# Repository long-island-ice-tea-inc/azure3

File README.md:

azure3
======

Engineering an 8x8x8 LED Cube

Directory Structure:
```
  azure3
     |
     +-----> pcb
     +-----> cam
     +-----> rpi
     |        |
     |        +----> lib
     |        |       |
     |        |       +----> bcm2835
     |        +----> src
     +-----> de1
```

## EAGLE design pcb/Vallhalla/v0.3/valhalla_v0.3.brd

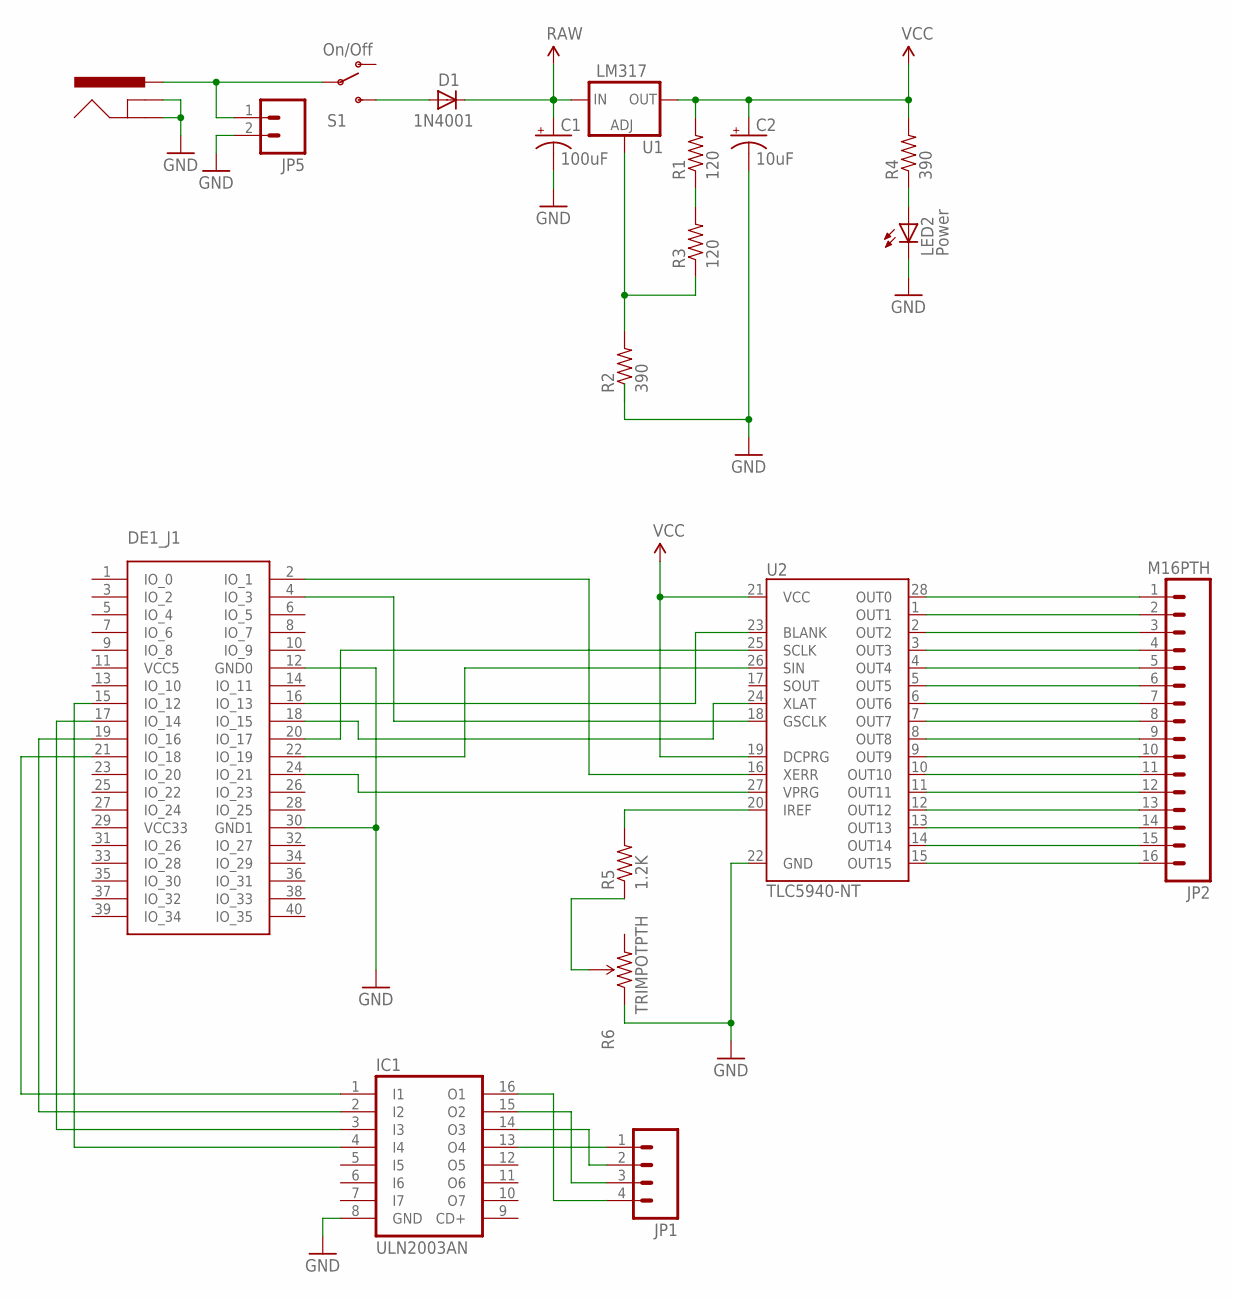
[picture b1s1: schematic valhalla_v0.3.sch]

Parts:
C1: 100uF; CPOL-RADIAL-100UF-25V
C2: 10uF; CPOL-RADIAL-10UF-25V
D1: 1N4001; DIODE-0.4
DE1_J1: DE1_GPIO_CON40"; 2X20
IC1: ULN2003AN; DIL16
J1: POWER_JACKPTH; POWER_JACK_PTH
JP1: M04PTH; 1X04
JP2: M16PTH; 1X16
JP5: M02PTH; 1X02
LED2: Power; LED5MM
R1, R3: 120; AXIAL-0.3
R2, R4: 390; AXIAL-0.3
R5: 1.2K; AXIAL-0.5
R6: TRIMPOTPTH; TRIM_POT_PTH
S1: On/Off; SWITCH-SPST
U1: LM317; TO220-ADJ
U2: TLC5940-NT; DIL28-3

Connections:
BLANK: DE1_J1.16 (IO_13), U2.23 (BLANK)
GND: C1.2 (-), C2.2 (-), DE1_J1.12 (GND0), DE1_J1.30 (GND1), IC1.8 (GND), J1.GND, J1.GNDBREAK, JP5.2, LED2.K (C), R2.P$1 (1), R6.1 (CCW), U2.22 (GND)
GSCLK: DE1_J1.4 (IO_3), U2.18 (GSCLK)
IREF: R5.P$2 (2), U2.20 (IREF)
unnamed: JP2.16, U2.15 (OUT15)
unnamed: D1.A, S1.3 (S)
unnamed: J1.PWR, JP5.1, S1.2
unnamed: JP2.15, U2.14 (OUT14)
unnamed: R5.P$1 (1), R6.2 (WIPER)
unnamed: JP2.14, U2.13 (OUT13)
unnamed: JP2.13, U2.12 (OUT12)
unnamed: LED2.A, R4.P$1 (1)
unnamed: JP2.12, U2.11 (OUT11)
unnamed: JP2.11, U2.10 (OUT10)
unnamed: JP2.10, U2.9 (OUT9)
unnamed: JP2.9, U2.8 (OUT8)
unnamed: JP2.8, U2.7 (OUT7)
unnamed: JP2.7, U2.6 (OUT6)
unnamed: JP2.6, U2.5 (OUT5)
unnamed: JP2.5, U2.4 (OUT4)
unnamed: JP2.4, U2.3 (OUT3)
unnamed: JP2.3, U2.2 (OUT2)
unnamed: JP2.2, U2.1 (OUT1)
unnamed: JP2.1, U2.28 (OUT0)
unnamed: DE1_J1.15 (IO_12), IC1.4 (I4)
unnamed: R1.P$1 (1), R3.P$2 (2)
unnamed: DE1_J1.17 (IO_14), IC1.3 (I3)
unnamed: R2.P$2 (2), R3.P$1 (1), U1.ADJ
unnamed: DE1_J1.19 (IO_16), IC1.2 (I2)
unnamed: DE1_J1.21 (IO_18), IC1.1 (I1)
unnamed: IC1.13 (O4), JP1.1
unnamed: IC1.14 (O3), JP1.2
unnamed: IC1.15 (O2), JP1.3
unnamed: IC1.16 (O1), JP1.4
RAW: C1.1 (+), D1.C, U1.IN
SCLK: DE1_J1.20 (IO_17), U2.25 (SCLK)
SIN: DE1_J1.22 (IO_19), U2.26 (SIN)
VCC: C2.1 (+), R1.P$2 (2), R4.P$2 (2), U1.OUT, U2.19 (DCPRG), U2.21 (VCC)
VCC5: DE1_J1.11 (VCC5)
VCC33: DE1_J1.29 (VCC33)
VPRG: DE1_J1.24 (IO_21), U2.27 (VPRG)
XERR: DE1_J1.2 (IO_1), U2.16 (XERR)
XLAT: DE1_J1.18 (IO_15), U2.24 (XLAT)

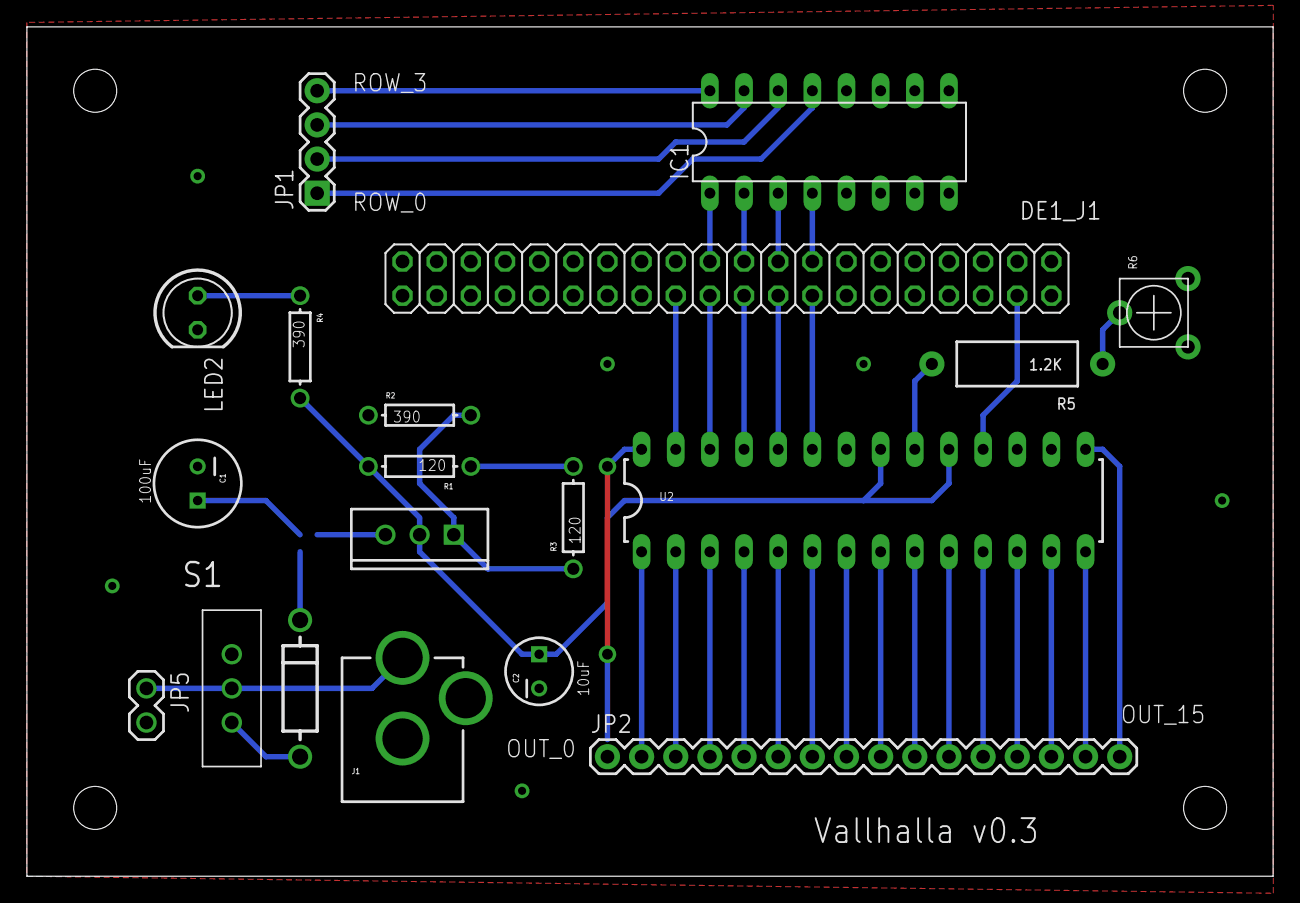
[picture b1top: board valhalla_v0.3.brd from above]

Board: 2 copper layers, 92.7 x 63.2 mm, 19 parts (0 on the bottom side), 41 nets.

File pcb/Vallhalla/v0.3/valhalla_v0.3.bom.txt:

Partlist exported from E:/WorK/github/azure3/pcb/Vallhalla/v0.3/valhalla_v0.3.sch at 3/5/2016 3:25 AM

Part   Value         Device           Package               Description                                                         
C1     100uF         CAP_POLPTH1      CPOL-RADIAL-100UF-25V Capacitor Polarized                                                 
C2     10uF          CAP_POLPTH2      CPOL-RADIAL-10UF-25V  Capacitor Polarized                                                 
D1     1N4001        DIODEPTH         DIODE-0.4             Diode                                                               
DE1_J1               DE1_GPIO_CON40"  2X20                  DE1 GPIO Connector                                                  
IC1    ULN2003AN     ULN2003AN        DIL16                 DRIVER ARRAY                                                        
J1     POWER_JACKPTH POWER_JACKPTH    POWER_JACK_PTH        Power Jack                                                          
JP1                  M04PTH           1X04                  Header 4                                                            
JP2    M16PTH        M16PTH           1X16                  1x16 .1" header                                                     
JP5                  M02PTH           1X02                  Header 2                                                            
LED2   Power         LED5MM           LED5MM                                                                                    
R1     120           RESISTORPTH1     AXIAL-0.3             Resistor                                                            
R2     390           RESISTORPTH1     AXIAL-0.3             Resistor                                                            
R3     120           RESISTORPTH1     AXIAL-0.3             Resistor                                                            
R4     390           RESISTORPTH1     AXIAL-0.3             Resistor                                                            
R5     1.2K          RESISTORPTH-1/2W AXIAL-0.5             Resistor                                                            
R6     TRIMPOTPTH    TRIMPOTPTH       TRIM_POT_PTH          Various small potentiometers for "set-and-forget" applications      
S1     On/Off        SWITCH-SPSTPTH   SWITCH-SPST           SPST Switch                                                         
U1     LM317         V_REG_317SINK    TO220-ADJ             Voltage Regulator                                                   
U2     TLC5940-NT    TLC5940-NT       DIL28-3               16-channel LED Driver with Dot Correction and Grayscale PWM Control

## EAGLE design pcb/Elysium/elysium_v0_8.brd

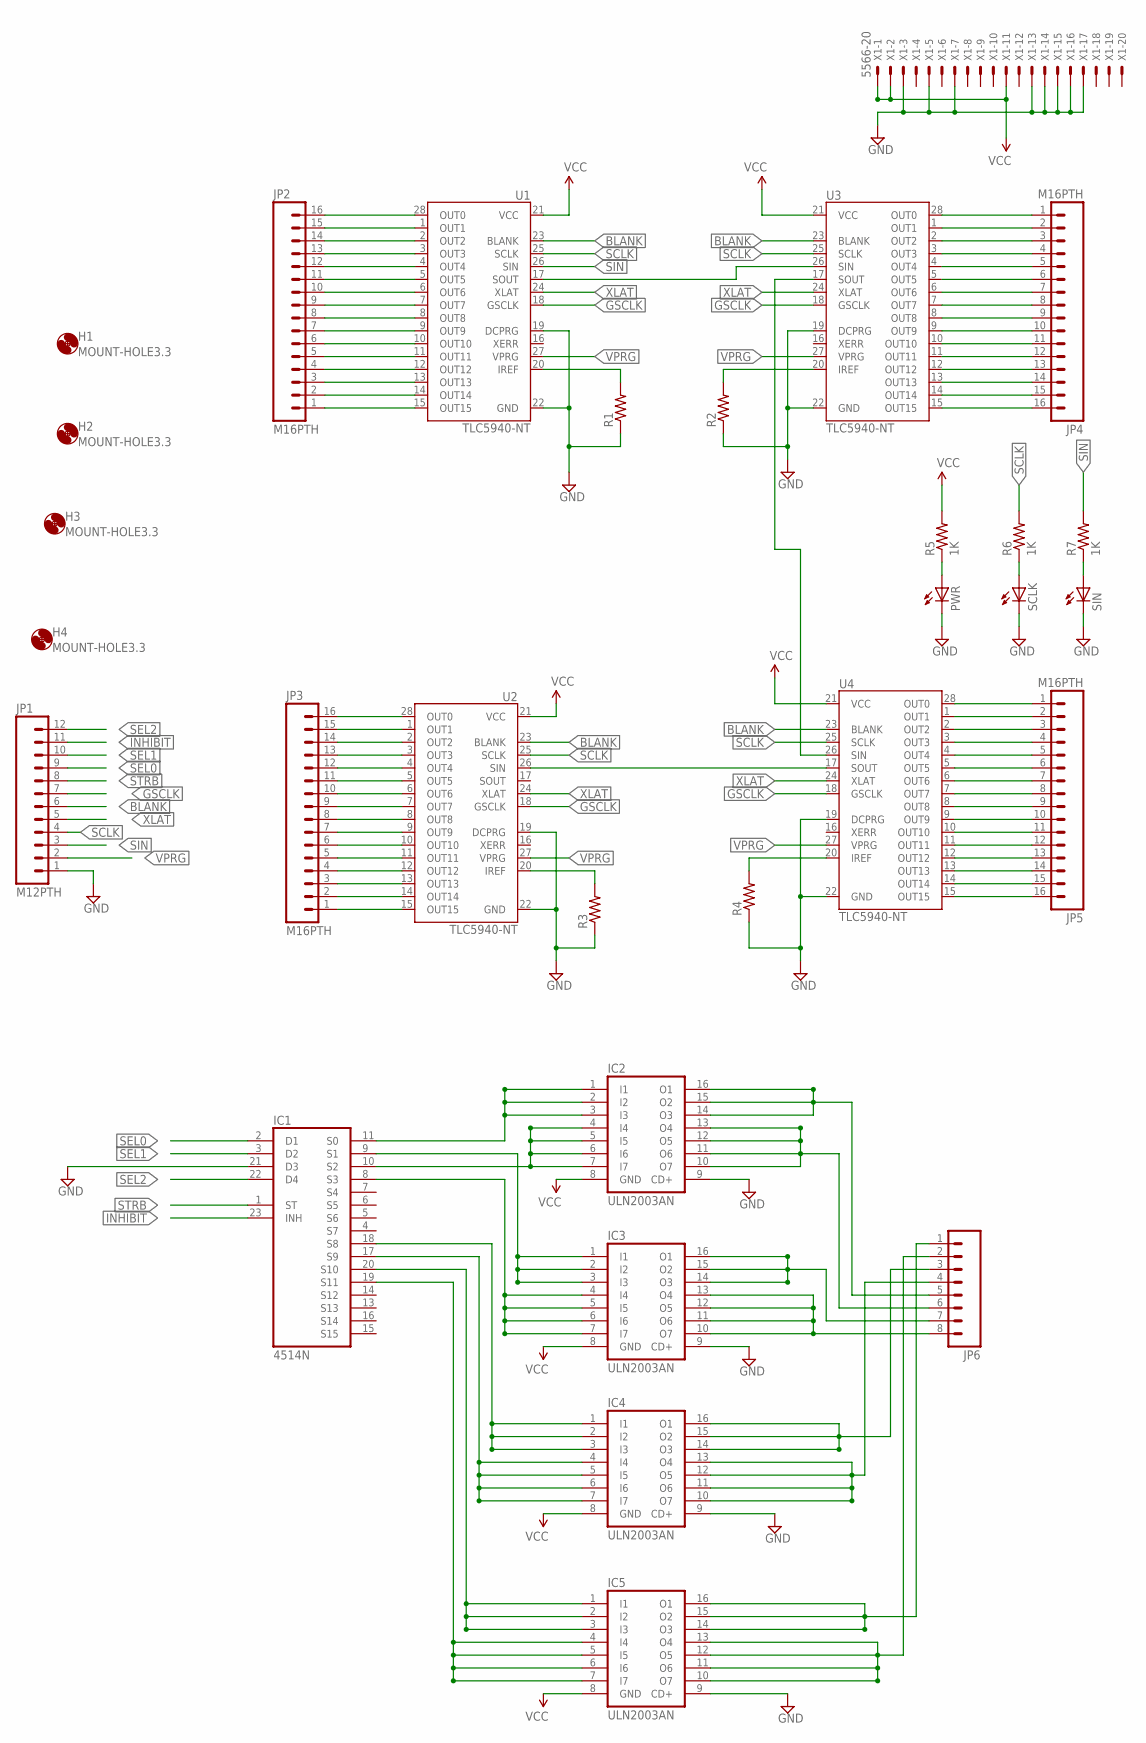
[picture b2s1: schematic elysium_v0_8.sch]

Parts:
H1, H2, H3, H4: MOUNT-HOLE3.3; 3,3
IC1: 4514N; DIL24-6
IC2, IC3, IC4, IC5: ULN2003AN; DIL16
JP1: M12PTH; 1X12
JP2, JP3, JP4, JP5: M16PTH; 1X16
JP6: M081X08; 1X08
PWR: LED5MM
R1, R2, R3, R4: RESISTOREZ; AXIAL-0.3EZ
R5, R6, R7: 1K; AXIAL-0.3EZ
SCLK: LED5MM
SIN: LED5MM
U1, U2, U3, U4: TLC5940-NT; DIL28-3
X1: 5566-20

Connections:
BLANK: JP1.6, U1.23 (BLANK), U2.23 (BLANK), U3.23 (BLANK), U4.23 (BLANK)
GND: IC1.12 (VSS), IC1.21 (D3), IC2.9 (CD+), IC3.9 (CD+), IC4.9 (CD+), IC5.9 (CD+), JP1.1, PWR.K (C), R1.P$1 (1), R2.P$1 (1), R3.P$1 (1), R4.P$1 (1), SCLK.K (C), SIN.K (C), U1.19 (DCPRG), U1.22 (GND), U2.19 (DCPRG), U2.22 (GND), U3.19 (DCPRG), U3.22 (GND), U4.19 (DCPRG), U4.22 (GND), X1.3, X1.5, X1.7, X1.13, X1.14, X1.15, X1.16, X1.17
GSCLK: JP1.7, U1.18 (GSCLK), U2.18 (GSCLK), U3.18 (GSCLK), U4.18 (GSCLK)
INHIBIT: IC1.23 (INH), JP1.11
unnamed: JP2.16, U1.28 (OUT0)
unnamed: JP2.15, U1.1 (OUT1)
unnamed: JP2.14, U1.2 (OUT2)
unnamed: JP2.13, U1.3 (OUT3)
unnamed: JP2.12, U1.4 (OUT4)
unnamed: JP2.11, U1.5 (OUT5)
unnamed: JP2.10, U1.6 (OUT6)
unnamed: JP2.9, U1.7 (OUT7)
unnamed: JP2.8, U1.8 (OUT8)
unnamed: JP2.7, U1.9 (OUT9)
unnamed: JP2.6, U1.10 (OUT10)
unnamed: JP2.5, U1.11 (OUT11)
unnamed: JP2.4, U1.12 (OUT12)
unnamed: JP2.3, U1.13 (OUT13)
unnamed: JP2.2, U1.14 (OUT14)
unnamed: JP2.1, U1.15 (OUT15)
unnamed: JP4.1, U3.28 (OUT0)
unnamed: JP4.2, U3.1 (OUT1)
unnamed: JP4.3, U3.2 (OUT2)
unnamed: JP4.4, U3.3 (OUT3)
unnamed: JP4.5, U3.4 (OUT4)
unnamed: JP4.6, U3.5 (OUT5)
unnamed: JP4.7, U3.6 (OUT6)
unnamed: JP4.8, U3.7 (OUT7)
unnamed: JP4.9, U3.8 (OUT8)
unnamed: JP4.10, U3.9 (OUT9)
unnamed: JP4.11, U3.10 (OUT10)
unnamed: JP4.12, U3.11 (OUT11)
unnamed: JP4.13, U3.12 (OUT12)
unnamed: JP4.14, U3.13 (OUT13)
unnamed: JP4.15, U3.14 (OUT14)
unnamed: JP4.16, U3.15 (OUT15)
unnamed: JP3.16, U2.28 (OUT0)
unnamed: JP3.15, U2.1 (OUT1)
unnamed: JP3.14, U2.2 (OUT2)
unnamed: JP3.13, U2.3 (OUT3)
unnamed: JP3.12, U2.4 (OUT4)
unnamed: JP3.11, U2.5 (OUT5)
unnamed: JP3.10, U2.6 (OUT6)
unnamed: JP3.9, U2.7 (OUT7)
unnamed: JP3.8, U2.8 (OUT8)
unnamed: JP3.7, U2.9 (OUT9)
unnamed: JP3.6, U2.10 (OUT10)
unnamed: JP3.5, U2.11 (OUT11)
unnamed: JP3.4, U2.12 (OUT12)
unnamed: JP3.3, U2.13 (OUT13)
unnamed: JP3.2, U2.14 (OUT14)
unnamed: JP3.1, U2.15 (OUT15)
unnamed: JP5.1, U4.28 (OUT0)
unnamed: JP5.2, U4.1 (OUT1)
unnamed: JP5.3, U4.2 (OUT2)
unnamed: JP5.4, U4.3 (OUT3)
unnamed: JP5.5, U4.4 (OUT4)
unnamed: JP5.6, U4.5 (OUT5)
unnamed: JP5.7, U4.6 (OUT6)
unnamed: JP5.8, U4.7 (OUT7)
unnamed: JP5.9, U4.8 (OUT8)
unnamed: JP5.10, U4.9 (OUT9)
unnamed: JP5.11, U4.10 (OUT10)
unnamed: JP5.12, U4.11 (OUT11)
unnamed: JP5.13, U4.12 (OUT12)
unnamed: JP5.14, U4.13 (OUT13)
unnamed: JP5.15, U4.14 (OUT14)
unnamed: JP5.16, U4.15 (OUT15)
unnamed: U1.17 (SOUT), U3.26 (SIN)
unnamed: U3.17 (SOUT), U4.26 (SIN)
unnamed: U2.26 (SIN), U4.17 (SOUT)
unnamed: R1.P$2 (2), U1.20 (IREF)
unnamed: PWR.A, R5.P$1 (1)
unnamed: R2.P$2 (2), U3.20 (IREF)
unnamed: IC1.11 (S0), IC2.1 (I1), IC2.2 (I2), IC2.3 (I3)
unnamed: IC1.9 (S1), IC3.1 (I1), IC3.2 (I2), IC3.3 (I3)
unnamed: R6.P$1 (1), SCLK.A
unnamed: R3.P$2 (2), U2.20 (IREF)
unnamed: R7.P$1 (1), SIN.A
unnamed: R4.P$2 (2), U4.20 (IREF)
unnamed: IC1.10 (S2), IC2.4 (I4), IC2.5 (I5), IC2.6 (I6), IC2.7 (I7)
unnamed: IC1.8 (S3), IC3.4 (I4), IC3.5 (I5), IC3.6 (I6), IC3.7 (I7)
unnamed: IC1.18 (S8), IC4.1 (I1), IC4.2 (I2), IC4.3 (I3)
unnamed: IC1.17 (S9), IC4.4 (I4), IC4.5 (I5), IC4.6 (I6), IC4.7 (I7)
unnamed: IC1.20 (S10), IC5.1 (I1), IC5.2 (I2), IC5.3 (I3)
unnamed: IC1.19 (S11), IC5.4 (I4), IC5.5 (I5), IC5.6 (I6), IC5.7 (I7)
unnamed: IC2.14 (O3), IC2.15 (O2), IC2.16 (O1), JP6.5
unnamed: IC2.10 (O7), IC2.11 (O6), IC2.12 (O5), IC2.13 (O4), JP6.6
unnamed: IC3.14 (O3), IC3.15 (O2), IC3.16 (O1), JP6.7
unnamed: IC3.10 (O7), IC3.11 (O6), IC3.12 (O5), IC3.13 (O4), JP6.8
unnamed: IC4.14 (O3), IC4.15 (O2), IC4.16 (O1), JP6.3
unnamed: IC4.10 (O7), IC4.11 (O6), IC4.12 (O5), IC4.13 (O4), JP6.4
unnamed: IC5.14 (O3), IC5.15 (O2), IC5.16 (O1), JP6.1
unnamed: IC5.10 (O7), IC5.11 (O6), IC5.12 (O5), IC5.13 (O4), JP6.2
SCLK: JP1.4, R6.P$2 (2), U1.25 (SCLK), U2.25 (SCLK), U3.25 (SCLK), U4.25 (SCLK)
SEL0: IC1.2 (D1), JP1.9
SEL1: IC1.3 (D2), JP1.10
SEL2: IC1.22 (D4), JP1.12
SIN: JP1.3, R7.P$2 (2), U1.26 (SIN)
STRB: IC1.1 (ST), JP1.8
VCC: IC1.24 (VDD), IC2.8 (GND), IC3.8 (GND), IC4.8 (GND), IC5.8 (GND), R5.P$2 (2), U1.21 (VCC), U2.21 (VCC), U3.21 (VCC), U4.21 (VCC), X1.1, X1.2, X1.11
VPRG: JP1.2, U1.27 (VPRG), U2.27 (VPRG), U3.27 (VPRG), U4.27 (VPRG)
XLAT: JP1.5, U1.24 (XLAT), U2.24 (XLAT), U3.24 (XLAT), U4.24 (XLAT)

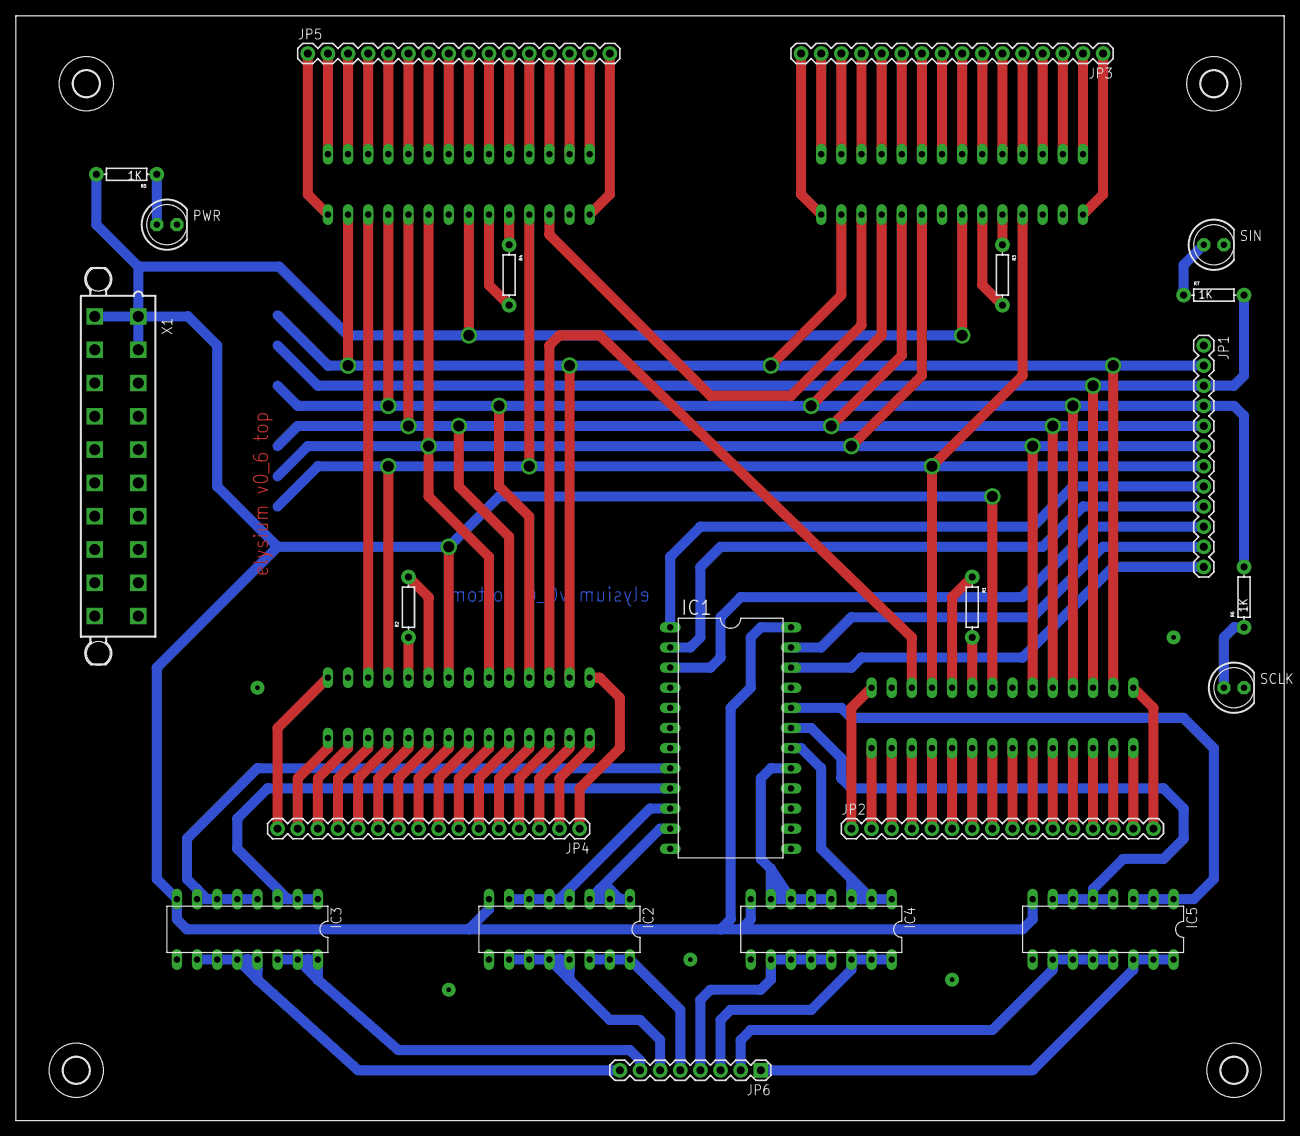
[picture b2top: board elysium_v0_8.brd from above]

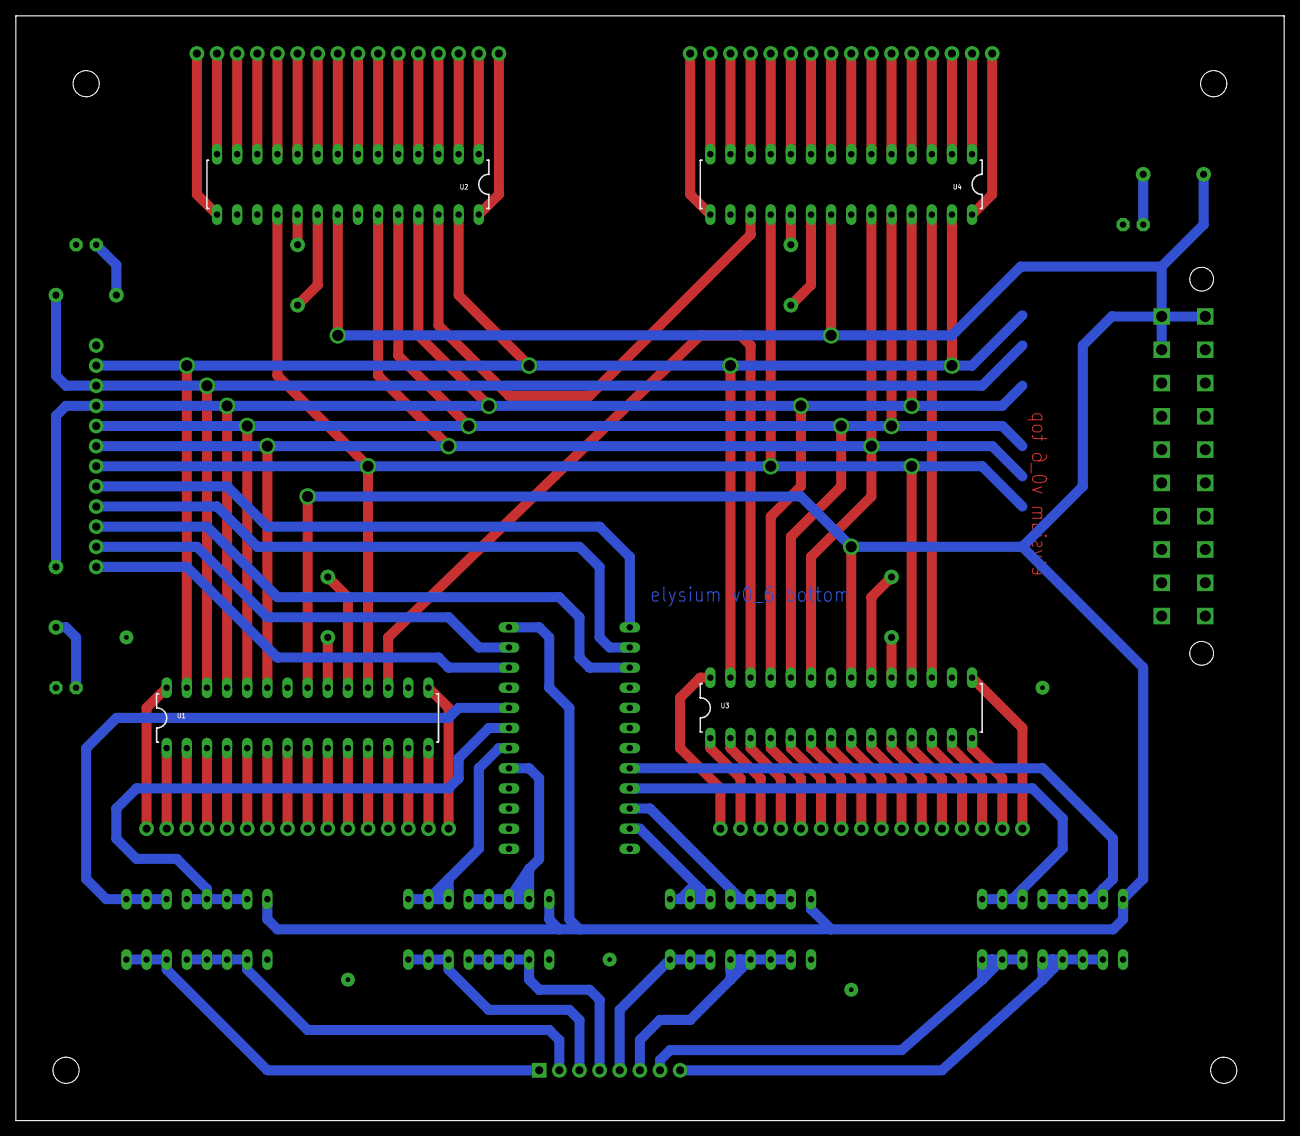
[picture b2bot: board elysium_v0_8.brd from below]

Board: 2 copper layers, 160.0 x 139.4 mm, 30 parts (4 on the bottom side), 103 nets.

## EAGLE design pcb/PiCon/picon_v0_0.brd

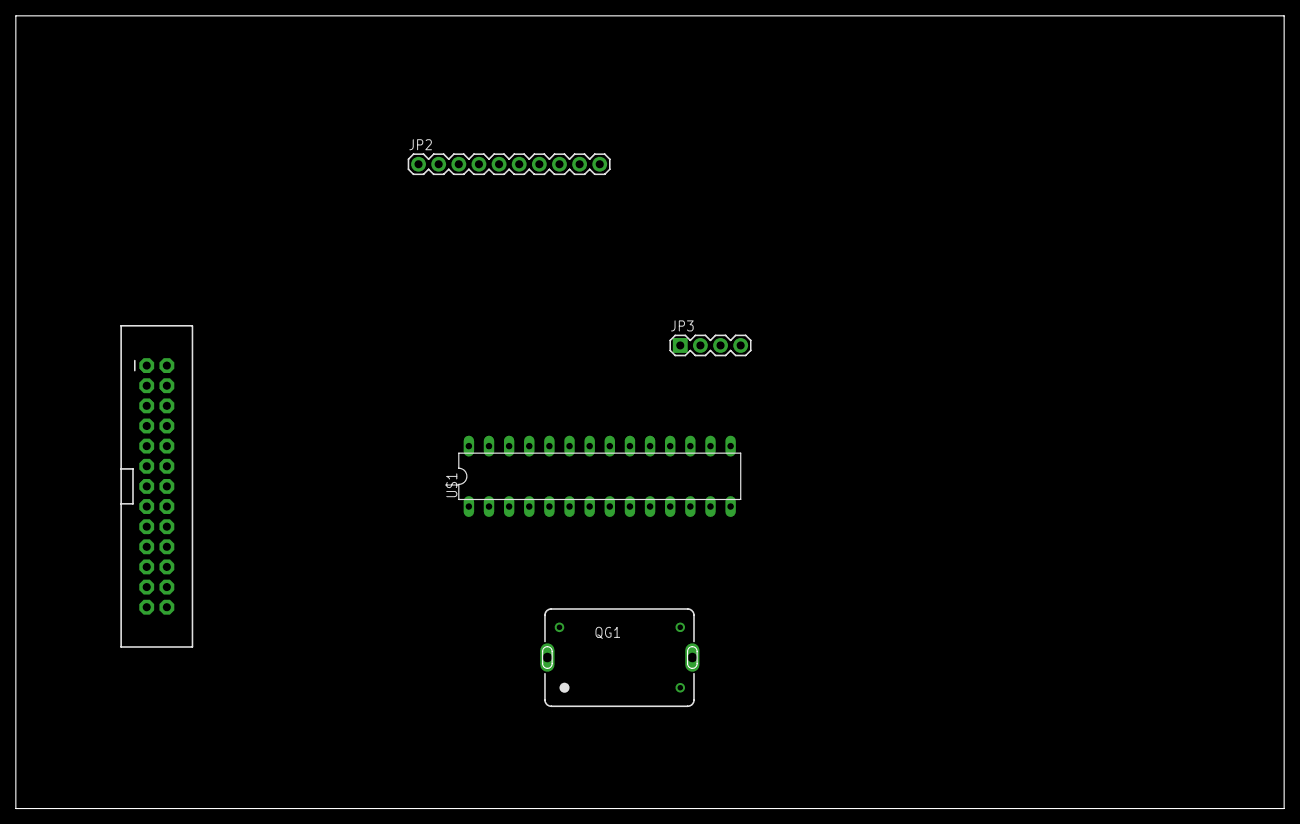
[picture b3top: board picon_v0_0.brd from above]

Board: 2 copper layers, 160.0 x 100.0 mm, 5 parts (0 on the bottom side), 3 nets, no tracks yet.

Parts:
JP1: RASPBERRYPI-GPIOPTH; 2X13-SHROUDED
JP2: M10"; 1X10
JP3: 1X04
QG1: TC46C; TC46
U$1: CD4068BDIL28-3; DIL28-3

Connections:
3.3V: JP1.1, JP1.17
5V: JP1.2, JP1.4
GND: JP1.6, JP1.9, JP1.14, JP1.20, JP1.25, QG1.7

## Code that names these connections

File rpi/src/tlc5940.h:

/*
 --------------------------------------------------------------------------
   Azure Cube - Copyright (C) 2014 Long Island Ice Tea Inc.

   This file is part of Azure Cube.

   Azure Cube is free; you can redistribute it and/or modify
   it under the terms of the GNU General Public License as published by
   the Free Software Foundation; either version 3 of the License, or
   (at your option) any later version.

   Azure Cube is distributed in the hope that it will be useful,
   but WITHOUT ANY WARRANTY; without even the implied warranty of
   MERCHANTABILITY or FITNESS FOR A PARTICULAR PURPOSE. See the
   GNU General Public License for more details.

   You should have received a copy of the GNU General Public License
   along with this program. If not, see <http://www.gnu.org/licenses/>.
 --------------------------------------------------------------------------
*/

/*
 --------------------------------------------------------------------------
 -- Project Code      : azure3
 -- Header Name       : tlc5940.h
 -- Author            : Manu
 -- Description       :
 --------------------------------------------------------------------------
*/

#ifndef tlc5940_H_
#define tlc5940_H_

#include <wiringPi.h>
#include <stdbool.h>

#define VPRG  0
#define XLAT  1
#define SIN   2
#define SCLK  3
#define BLANK 4
#define GSCLK 7

#define NUM_CHANNELS  16 
#define NUM_DCBITS    8
#define NUM_GSBITS    12
#define NUM_CHIP      4
#define NUM_GSCLK     4096

#define GSCLK_FREQ    2400000
#define BLANK_DELAY   1
//#define BLANK_USE_NANO

typedef struct gsArray  {
        short chan[NUM_CHANNELS];
} gsArray_t;

bool FirstCycle;

PI_THREAD (driveGSCLK_BLANK); 

void setupTLC5940 ();

void dotCorrectTLC5940 ();

void initTLC5940 ();

void updateTLC5940 ();

void setVPRG ();

void clrVPRG ();

void setXLAT ();

void clrXLAT ();

void setSIN ();

void clrSIN ();

void setSCLK ();

void clrSCLK ();

void setBLANK ();

void clrBLANK ();

void setGSCLK ();

void clrGSCLK ();

#endif /* tlc5940_H_ */

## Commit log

2014-01-22 Added sumodule wiki
2014-01-22 Added basic template to wiki home
2014-01-25 Added PCB Files
2014-01-25 Added directory structure
2014-01-25 Fixed Directory display issues
2014-01-26 Added rev_0_4 board
    Rev 0_4 has status LEDs with ground planes.
2014-01-26 Initial version
2014-01-28 Added blank bill of materials file for elysium
2014-02-02 Added TLC5940 Drivers - working on breadboard
2014-03-09 PCB Schematics revs 5 & 6
2014-03-14 Added mounting holes to v0.6 PCB.
2014-03-16 Added rev_0_7
2014-03-16 Added new project for PiCon and base CD4068 library
2014-03-16 Mirrored
2014-03-17 Added LIT Library
    CD4068B device inside.
2014-03-17 Misc changes
2014-03-19 Added decoder & current amplifier in rev08
2014-03-19 Added Datasheets
2014-03-19 Misc updates
2016-01-13 misc
2016-01-13 Commit of valhalla_v0.1
2016-01-17 Added Sparkfun CAM library
2016-01-17 Misc changes based on availability of components
2016-01-20 Added v0.2
    Moved traces to bottom layer
2016-03-04 Version 3
    Added ULN2003

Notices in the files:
parts and their libraries:
SparkFun-DigitalIC: Licensing: CC v3.0 Share-Alike You are welcome to use this library for commercial purposes.
